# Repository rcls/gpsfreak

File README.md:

GPSfreak — GPS Disciplined Frequency Generator
=================================================

[  ](images/outside-big.jpg)
GPSfreak is a flexible, programmable, high-accuracy, low-jitter, frequency
generator, using GPS as a reference.

There are 5 outputs via SMA connectors, with 4 separately programmable
frequencies derived from 2 PLLs.

The outputs are driven by a Texas Instruments LMK05318b clock generator, and a
U-Blox MAX-10 GPS receiver providing the overall frequency reference.

Power and data are supplied via a USB-C connector (USB FS data rate).  The GPS
unit is available over USB as a CDC ACM serial port.  In addition, there are USB
end-points for device control via the CPU, and Python scripts to drive this.

The hardware is developed using KiCad, and the software using Rust and Python.
There are pdfs of the [schematic](gpsfreak-sch.pdf) and [PCB layout](gpsfreak-pcb.pdf).

License
=======

The hardware designs in this project are all licensed under CERN Open Hardware
Licence, strongly reciprocal, CERN-OHL-S.  (`cern_ohl_s_v2.txt`).

All software in this project is licensed under the GNU GPL v3.  (`COPYING.txt`)

Connectors
==========

[  ](images/inside-big.jpg)

**Outputs 1+** and **1–**
: Complementary high frequency, 3 MHz to 1.6 GHz, 11 dBm nominal output power.
  These can be used together as a differential pair.  AC coupled.

**Output 2**
: High frequency.  3 MHz to 1.6 GHz, 11 dBm nominal output power.  AC coupled.
  There is provision for a balun on the PCB to raise the output power to 14 dBm.

**Output 3**
: Low frequency 3.3 V CMOS.  Sub-1 Hz to 325 MHz.  DC coupled.

**Output 4**
: Mid frequency 3.3 V CMOS.  3 MHz to 325 MHz.  DC coupled.

**GPS Input** for an active L1 and/or L5 GPS antenna.  It provides 3.3 V (or
5 V) antennae power.  The voltage selection is a strap resistor on board.

**USB-C**
: Power (approx 2 W) and data (USB FS).

The high frequency outputs provide complete coverage of 3 MHz to 800 MHz with ≈
pico-Hertz resolution, and then select frequencies to 1.6 GHz.  (There is a
region around 520 MHz where the LMK05318b is operated outside its documented
range, but I have seen no issue with this.)

The outputs are all nominally 50 Ω.  In fact, the LMK05318b appears to have
current-source outputs, so the drive impedance of the high-frequency outputs is
high.  The two CMOS level outputs are each driven by a TLV3601 comparator, from
the datasheet this appears to be a reasonable match for 50 Ω.

There are also pads for 3 internal U.Fl connectors.  One provides an additional
output, one a secondary reference clock input to the LMK05318b, and the last an
output of the GPS timepulse signal.  A possible use is to divert the GPS
timepulse to an external Rubidium clock, and then use that to drive the
secondary reference.

GPS
===

This is a U-Blox MAX-F10S.  (Building the board with other U-Blox MAX or
compatible devices is possible.  The firmware should work with any U-Blox MAX-10
or later device.)

Status LED
==========

There is a status LED next to the USB connector.  This is a three colour RGB
LED.  The LED lights green or red to indicate that the device has PLL lock.
Additionally, the blue component indicates USB activity.

Housing
=======

The board outline is just under 80 mm × 50 mm.  A matching extruded aluminium
housing (80 mm × 50 mm x 20 mm) can be readily obtained from websites such as
AliExpress.

There are small KiCad projects for end-plates (`end-in.kicad_pro` and
`end-out.kicad_pro`), with appropriately sized holes for the connectors and LED.
The screw holes can be counter-sunk with a drill as appropriate.

I recommend checking the board for fit before soldering the components on the
edges (USB and SMA connectors, and the LED).  If necessary, the edges of the
board can be sanded down slightly with sandpaper.

Heat-sinking
------------

The LMK05318b generates a bit of heat, and the board may reach temperatures
30 °C above ambient.  This should not be a problem, but provision is made to
heat-sink the rear of the PCB to the case.

There is an 11 mm × 7 mm exposed copper area backside to the LMK05318b.  Solder
a 2 mm thick copper slug to this, and then cover with a 1.5 mm thick thermal
pad.  The clearance between PCB and housing is 3 mm, so inserting the board into
the housing will apply gentle pressure to the thermal pad.  Chamfer the
appropriate edge of the housing with a file to make inserting the assembly
easier.

(You can find e.g., 2 mm × 10 mm × 100 mm copper bars on AliExpress, from which
an appropriate slug can be cut with a hacksaw.)

Software
========

The device software is a mix of on-board firmware, and Python scripts
(`py/freak.py`) to communicate with the device.  These should work on any OS
that pyusb supports.

The firmware is pretty dumb.  All the frequency planning logic is in the Python
scripts, with the firmware essentially just passing through commands to the GPS
and clock generator.  Frequency plans may be written to flash for autonomous
operation with no USB.

Firmware updates are done via USB DFU.  There is also a Skedd connector breaking
out the CPU SWD with a standard six pin connection.  The CPU boot pin is taken
to a 0.1" header, which can be used to access DFU in case of corrupted firmware.

The Python scripts should work with Python 3.10 or later.

Board Manufacture
=================

The schematic has JLCPCB part numbers for most components.  Components that I've
hand assembled are marked with `exclude from BOM´ and may or may not have the
part number.  Review and change these to suit.

The Makefile should generate Gerber and component files, just run `make`.

The I/O traces (GPS, clock outputs, and USB) are sized for appropriate impedance
on the JLCPCB 4-layer default stack-up (7628).  None of them should be
especially critical, but if you use a different stack-up, then it is worth
double-checking and adjusting them.

Components that I have hand-soldered in preference to using JLCPCB assembly:

* JLCPCB doesn't stock the MAX-F10S.  It is fairly easy to hand-solder.  They do
  stock the cheaper MAX-M10S.
* The USB-C connector, saving a handling fee.
* The SMA connectors.  Position them carefully as they need to align with the
  end-plate holes!  These are edge-launch connectors for a 1.6 mm PCB.  You
  can get these cheaply in bulk from AliExpress.  The ones I used have approx
  12 mm thread length, 18_mm total length including leads.
* The 0402 antennae bias inductor.  The pads are designed for easy hand
  soldering (one is bigger than the other, solder the smaller pad first).
* Likewise, the antennae power PTC fuse and the 74HC1G07 for antennae-short
  detection are hand-soldered, to save assembly costs.  The 74HC1G07 is
  optional.
* The three C0G/NP0 loop-filter caps (C78, C79, C92).
  JLCPCB doesn't have the exact parts.
* The LED.
* The TVS protection diodes I have never populated.  The 0402 pads are designed
  for hand-soldering just like the inductor above.

If you want to keep assembly costs down, then hand soldering many of the ICs is
an option.  This is especially true if you only want one board, as most
manufacturers insist on making multiple!

There is enough space between most of the ICs and surrounding passive components
to get a soldering iron in, but if you are unsure of your soldering equipment
and skills, then review the board layout before committing yourself to that.

Initial Software Install and Configuration
==========================================

This is a rather manual process at the moment.

Firmware build & install
------------------------

For the firmware build, install a recent \`nightly´ rust compiler, along with
cargo, along with the `thumbv8m.main-none-eabihf` target to support the CPU.

Build the firmware with `cargo b`.  This is an alias to build with the correct
compiler options.  The .elf file is left in
`target/thumbv8m.main-none-eabihf/release/freak.elf`.

The initial firmware install can either be done via a SWD dongle (J-Link or
similar) or via DFU USB.  Most SWD programmers support `.elf` files directly.
`dfu-utils` is an unfriendly command line tool, the `dfu.sh` script works for
me.  Note that the shell script assumes you have only one DFU capable device
attached.

The `freak` tool is written in Python.  You need Python 3.10 or later.  The only
additional Python module you need should be `pyusb`, which can be installed
using `pip`.

Initial configuration
---------------------

Run `freak config manufacture`.  This will upload a fairly sane default
configuration for the device, with all outputs at 10 MHz, except for 1 Hz on
output 3.  The DPLL bandwidth is set to 0.3 Hz, which is quite low, and requires
a decent TCXO to achieve lock

If you want to customize the configuration:
 * The uploaded default LMK05318b configuration expects a 8844582 Hz reference
   from the GPS unit.  If you choose something different, be careful about
   near-integer aliasing from the GPS.
 * Loss-of-lock LED indication relies on the GPS turning off that reference
   when GPS signal is lost.  Don't configure the GPS to output the reference
   with no GPS signal (CFG-TP-FREQ_TP1).
 * You can use TICS/Pro to customize the LMK05318b configuration.  Start
   from `py/freak/bw0p3hz_ref8844582.tcs` or another in py/freak/*.tcs.
 * Note that TICS/Pro tends to silently change the lock parameters to values
   that are not good for this hardware.  After running the DPLL script, go to
   the 'Reference Validation' and 'DPLL and BAW flags' tabs, and ensure that
   the Early Window Detector and Lock Thres values are both at least 17 ns.
 * Setting the host-side UART baud rate **must** be done using `freak gps baud`,
   the normal OS serial port baud rate setting is ignored.  I use
   230400 baud; the default 9600 is awfully slow.
 * The initial configuration mentioned above sets `TP-ALIGN_TO_TOW_TP1` to
   False.  This improves short term frequency accuracy, at the expense of a
   small (≈ 3 ppt) long term inaccuracy.

Internal Control Lines
======================

The CPU has various control lines to the GPS and clock chip.  There is UART to
the GPS, and all are on an I2C bus.  In addition, there are connections to:

* EXTINT and RESET lines on GPS.
* PDN, STATUS0, STATUS1 / FDEC and GPIO2 / FINC on the clock chip.  The latter
  two potentially allow some degree of frequency modulation to be achieved e.g.,
  a basic low bit-rate FSK.

Hardware Options
================

The three U.Fl connectors can be soldered.  The GPS timepulse output also
requires soldering a 50 Ω 0603 or similar termination component.

There are pads for a balun on output 2.  If wanted, remove the two 0603
resistors, and solder a 2:1 impedance balun, for a 3 dB increase in output
power.

Before building a device:
 * There are a lot of closely spaced 0402 components on the board.  Unless you
   want the soldering practice, get the majority of the components soldered by
   the board manufacturer.  Most components have JLCPCB part numbers.
 * Review the BOM lists and PCB layout, and check that you are comfortable
   with any components you are going to hand solder.

Component Substitutions
-----------------------

Some notes on possible component substitutions / changes.

**GPS** Any U-Blox MAX-10 is a drop-in replacement.  The software should be
compatible with any U-Blox unit with the newer configuration messages (F9 and
later).  Hardware-wise, any U-Blox 18-pin module should be electrically
compatible.

**LMK05318b** Do not use the non-`b´ LMK05318:
  * With the 3.3 V swing on the reference input, you need to DC couple it, which
    is only supported on the `b´ variant.
  * The software uses the programmable PLL2 denominator.

**C0G/NP0 caps** These are probably overkill for the loop-filter caps.  Feel
free to replace with (smaller and cheaper) X5R / X7R.  In that case I suggest
use parts with a voltage rating of at least 10 V, to minimize the X5R / X7R
voltage dependence.  C78 is only in the schematic because the physically larger
C79 is some distance from the LMK05318b.  If you use smaller components, then
change C78 to 470 nF and remove C79.

If you don't want to hand-solder C78, you could reduce the value to 330 pF
(which JLCPCB has as a basic component).

**Ferrite Beads** I used 100 Ω @ 100 MHz, because JLCPCB had them as basic parts
(no loading fee).  The TI evaluation board has 220 Ω @ 100 MHz.  The choice is
probably not critical, but if you use parts with DC resistance above 0.1 Ω then
double check power consumption and voltage drop on the various voltage rails.

I'm not sure how much difference the ferrite beads make in practice.  If you
remove them entirely, then all the point-of-load 10 µF caps on the power rails
can be replaced by 0.1µF caps.  (Don't change C77, C91 and C93 though.)

**Filter caps** I've used 0402 10 µF caps, where-as the LMK05318b datasheet
suggests 10 µF 0402 plus 0.1 µF 0201.  The main reason is that they are cheaper
with JLCPCB (0201 caps incur loading and assembly fees).

**CPU** Basically any QFN-32 STM32 with USB should be a drop-in replacement
hardware-wise, and require few software modifications—likely only the CPU
initialization and USB clocking will need to change.  Likewise, a CPU in a
different package should require only minor board modifications.

**Voltage regulators** I provisioned 1.8 V as well as 3.3 V in order to reduce
power dissipation.  TI suggests using LDOs to reduce noise.  Having the two
switching regulators before the LDOs reduces power consumption and heating,
without them the LDO would probably overheat.  Beyond that, the power supply
circuitry is fairly arbitrary.

If you switch to a CPU with that supports 1.8 V I/O then you could run the GPS
at 1.8 V also (but in that case, you'll need to supply 3.3 V to the GPS antennae
bias.)

The feedback divider resistors are chosen to avoid JLCPCB loading fees.
Additionally, fine-grained margining of the LDO output voltages can be achieved
by replacing the two 0603 resistors, R56 and R66.

**SMA Connectors** Feel free to replace with through-hole rather than
edge-mount.  In that case, also straighten the board edge, as you no longer need
the cut-outs.  You will need to adjust the position of the mounting-holes in the
end-plates appropriately.

**Programming Header** This can be removed, or swapped for whatever you fancy.
You need to keep one of either the SWD header, or else the boot-pin header, in
order to load firmware.  (Once you have functioning firmware installed, you can
upgrade purely via software command.)

**Temperature Sensor** Populating this is optional.

**LED** This is a common 1206 edge-mount footprint RGB LED.  If you use a
different part, then double or triple check the footprint, and note the odd pad
numbering.

**PTC Fuse** U-Blox example schematics just use a current limiting resistor.
Which would be cheaper. The 74HC1G07 logic gate for antennae short-circuit
sensing is optional.

Hardware Versioning
===================

[TODO - change pin.] CPU pin 13 A7 is reserved for hardware versioning.  The
plan is to use the CPU ADC to read a resistor voltage divider.  To change the
hardware revision, drive with a resistor divider, approx. 10k Thevenin
resistance or less, to N / 25 × VDD, where N is the revision number.  This is
revision 0, so the pin is grounded.

Cost Reduction Opportunities
============================

The MAX-M10S is a cheaper alternative to MAX-F10S, but still performs OK, albeit
with a slightly worse short-term frequency accuracy.

The TCXO can be replaced by a cheaper one.  The phase noise to worry about is
capped above at around 18 kHz by the BAW oscillator, and at low frequencies by
the GPS output.  Using a TCXO rather than an XO is probably not essential, but
does allow us to run the LMK05318b at low bandwidth and smooth out the
once-per-second frequency adjustments from the GPS unit.

The CPU is overkill.  With the current arrangement of dumb firmware & all the
smarts in the Python scripts, a low-end CPU would be just fine.

The temperature sensor is only for development.  Once we know how much heat the
board generates, we can drop it.  Or just use a 1 ¢ thermistor.  There is also
the CPU temperature sensor.

Evaluate whether or not the C0G capacitors on the loop filter are worthwhile.  I
suspect not in realistic conditions.  The 0.47 µF C0G cap could also be replaced
by a through-hole film cap.

The super cap is more or less redundant.  It's only to speed up GPS start-up
after a short power outage, but we are likely to be always on anyway.

The output balun on output 2 is not worth the cost.  I've marked it as DNP
in the schematic.

The `freak` tool
================

The `freak` tool can perform various operations as well as setting the output
frequencies.  Everything has a `--help` option which is hopefully helpful.

`freak freq` with no arguments displays the current output frequencies.  Give it
arguments to set the output frequencies.  The units default to MHz, but an
explicit unit of Hz, kHz or GHz may be given.  Rational numbers (e.g., 100/3)
are accepted, and avoid rounding errors inherent with decimals (33.333333).

`freak plan` can carry out the frequency planning computations without writing
them to the device.  This is useful to explore what is possible.

`freak drive` can display and set the various output drive strengths.

`freak clock get/set` and get and set individual clock generator registers.  The
TI documentation lists most but not all of these.  The file
`py/freak/lmk05318b.list` has a few additions that I've gleaned from other
sources.

`freak gps get/set` likewise get and set GPS config registers.

For more advanced programming of the LMK05318b, your best option is to generate
a `.tcs` file with the TI TICS/Pro tool, and write to the device with `freak
clock upload`.

`freak info`, `freak clock status`, `freak gps info` and `freak gps status` all
output various bits of hardware information and status, in varying degrees of
understandability.

`freak gps changes` shows the difference between the current GPS configuration
and the factory defaults.

`freak clock dump` or `freak gps dump` print the entire clock generator or GPS
configuration, respectively.

Known Issues
============

If frequency planning fails, then `freak` tends to die with an unfriendly
assertion failure rather than a useful error message.  Ditto various other error
conditions.  Problems with the communication to the GPS unit likely result in
hangs.

Change Log
==========

Current
-------

Enlarge the exposed pad backside to the clock chip to be 11 mm × 7 mm instead of
7 mm square.

Don't have the LED overhanging the board edge.  Change all the LED resistors to
0603 for easier swapping.  Plate the panel cut-out opening for the LED.

Remove the unnecessary strap resistor on the GPS timepulse U.Fl connector.

Hardware version 1.0
--------------------

Two built.  Major revision from prototype.  git rev 496bb8c98727dc07.

Prototype
---------

Hardware was git rev 24c0655742e6f093.  Only one built.

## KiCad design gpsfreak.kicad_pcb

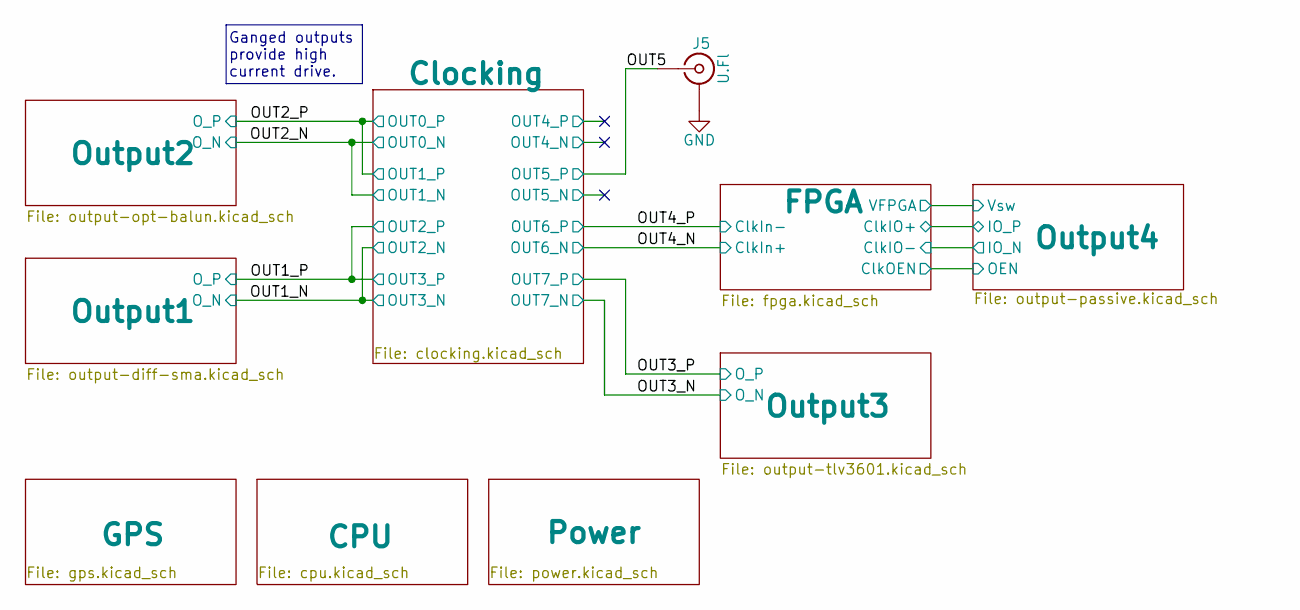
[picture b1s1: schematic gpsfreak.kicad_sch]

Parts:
J5: U.Fl; U.FL_Hirose_U.FL-R-SMT-1_Vertical

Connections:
/OUT5: J5.1 (In); also elsewhere on the board
GND: J5.2 (Ext); also elsewhere on the board

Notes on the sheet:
Ganged outputs provide high current drive.

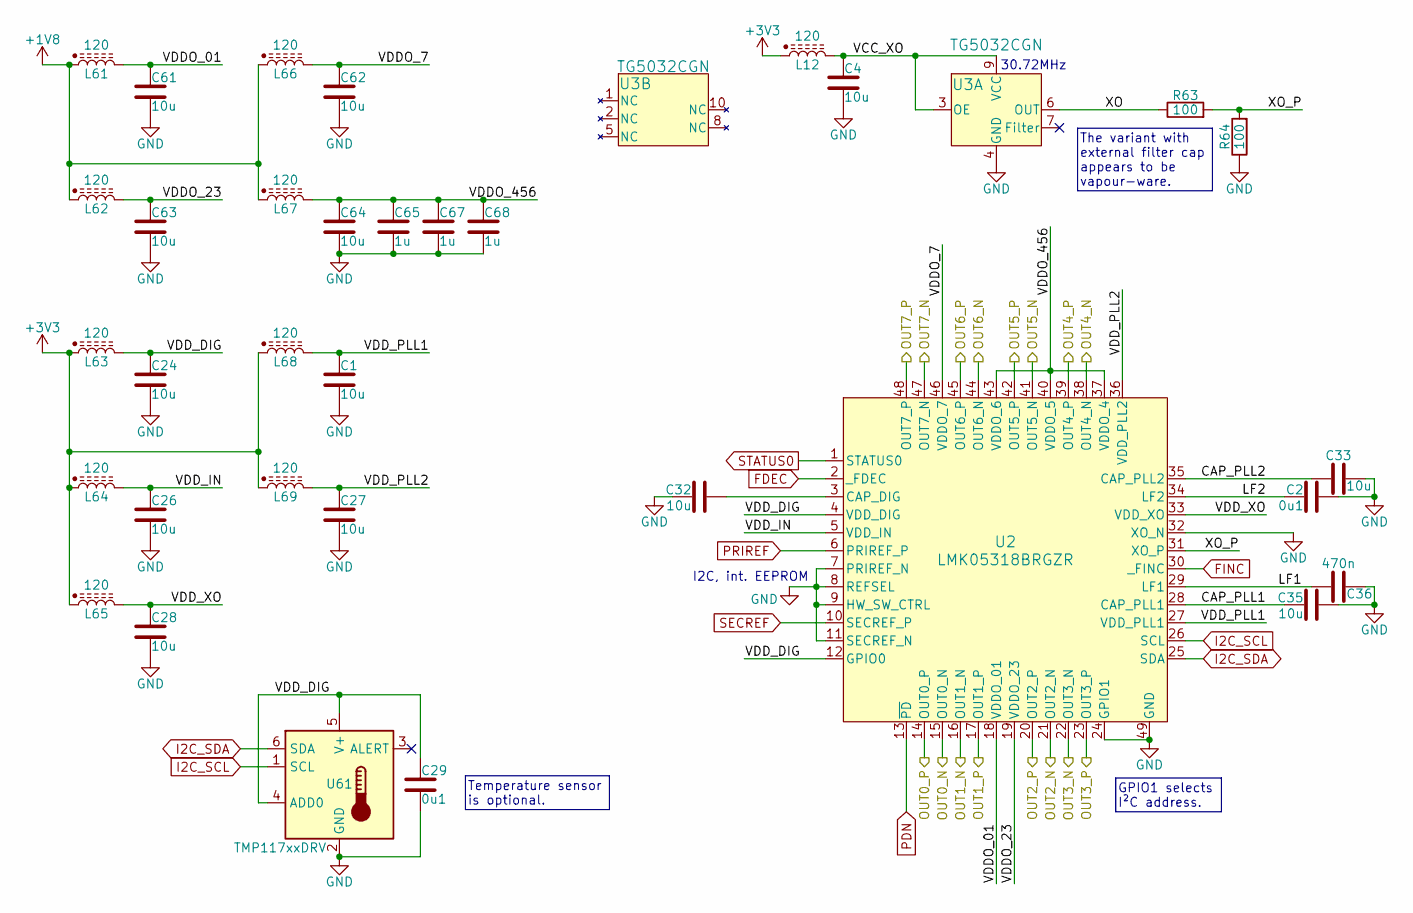
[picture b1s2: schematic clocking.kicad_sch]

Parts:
C1, C4, C24, C26, C27, C28, C32, C33, C35, C61, C62, C63, C64: 10u; C_0402_1005Metric; LCSC C315248
C2: 0u1; C0704; LCSC C20044553
C29: 0u1; C_0402_1005Metric; LCSC C307331
C36: 470n; C_1206_3216Metric; LCSC C21082486
C65, C67, C68: 1u; C_0402_1005Metric; LCSC C52923
L12, L61, L62, L63, L64, L65, L66, L67, L68, L69: 120; L_0603_1608Metric; LCSC C14709
R63, R64: 100; R_0402_1005Metric; LCSC C25076
U2: LMK05318BRGZR; QFN-48-1EP_7x7mm_P0.5mm_EP5.1x5.1mm; LCSC C3611586
U3: TG5032CGN; QFN10_TG5032CGN 40.0000M-CAGHNA0_EPS; LCSC C2891970
U61: TMP117xxDRV; WSON-6-1EP_2x2mm_P0.65mm_EP1x1.6mm

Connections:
+1V8: L61.1, L62.1, L66.1, L67.1; also elsewhere on the board
+3V3: L12.1, L63.1, L64.1, L65.1, L68.1, L69.1; also elsewhere on the board
/Clocking/CAP_PLL1: C35.2, U2.28 (CAP_PLL1)
/Clocking/CAP_PLL2: C33.2, U2.35 (CAP_PLL2)
/Clocking/LF1: C36.1, U2.29 (LF1)
/Clocking/LF2: C2.1, U2.34 (LF2)
/Clocking/OUT4_N: U2.38 (OUT4_N)
/Clocking/OUT4_P: U2.39 (OUT4_P)
/Clocking/OUT5_N: U2.41 (OUT5_N)
/Clocking/VCC_XO: C4.1, L12.2, U3.3 (OE), U3.9 (VCC)
/Clocking/VDDO_01: C61.1, L61.2, U2.18 (VDDO_01)
/Clocking/VDDO_7: C62.1, L66.2, U2.46 (VDDO_7)
/Clocking/VDDO_23: C63.1, L62.2, U2.19 (VDDO_23)
/Clocking/VDDO_456: C64.1, C65.1, C67.1, C68.1, L67.2, U2.37 (VDDO_4), U2.40 (VDDO_5), U2.43 (VDDO_6)
/Clocking/VDD_DIG: C24.1, C29.1, L63.2, U2.4 (VDD_DIG), U2.12 (GPIO0), U61.4 (ADD0), U61.5 (V+)
/Clocking/VDD_IN: C26.1, L64.2, U2.5 (VDD_IN)
/Clocking/VDD_PLL1: C1.1, L68.2, U2.27 (VDD_PLL1)
/Clocking/VDD_PLL2: C27.1, L69.2, U2.36 (VDD_PLL2)
/Clocking/VDD_XO: C28.1, L65.2, U2.33 (VDD_XO)
/Clocking/XO: R63.1, U3.6 (OUT)
/Clocking/XO_P: R63.2, R64.2, U2.31 (XO_P)
/OUT1_N: U2.21 (OUT2_N), U2.22 (OUT3_N); also elsewhere on the board
/OUT1_P: U2.20 (OUT2_P), U2.23 (OUT3_P); also elsewhere on the board
/OUT2_N: U2.15 (OUT0_N), U2.16 (OUT1_N); also elsewhere on the board
/OUT2_P: U2.14 (OUT0_P), U2.17 (OUT1_P); also elsewhere on the board
/OUT3_N: U2.47 (OUT7_N); also elsewhere on the board
/OUT3_P: U2.48 (OUT7_P); also elsewhere on the board
/OUT4_N: U2.44 (OUT6_N); also elsewhere on the board
/OUT4_P: U2.45 (OUT6_P); also elsewhere on the board
/OUT5: U2.42 (OUT5_P); also elsewhere on the board
FDEC: U2.2 (_FDEC); also elsewhere on the board
FINC: U2.30 (_FINC); also elsewhere on the board
GND: C1.2, C2.2, C4.2, C24.2, C26.2, C27.2, C28.2, C29.2, C32.1, C33.1, C35.1, C36.2, C61.2, C62.2, C63.2, C64.2, C65.2, C67.2, C68.2, R64.1, U2.7 (PRIREF_N), U2.8 (REFSEL), U2.9 (HW_SW_CTRL), U2.11 (SECREF_N), U2.24 (GPIO1), U2.32 (XO_N), U2.49 (GND), U3.4 (GND), U61.2 (GND), U61.7 (GND); also elsewhere on the board
I2C_SCL: U2.26 (SCL), U61.1 (SCL); also elsewhere on the board
I2C_SDA: U2.25 (SDA), U61.6 (SDA); also elsewhere on the board
unnamed: C32.2, U2.3 (CAP_DIG)
PDN: U2.13 (~PD); also elsewhere on the board
PRIREF: U2.6 (PRIREF_P); also elsewhere on the board
SECREF: U2.10 (SECREF_P); also elsewhere on the board
STATUS0: U2.1 (STATUS0); also elsewhere on the board

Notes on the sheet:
I2C, int. EEPROM
30.72MHz
Temperature sensor is optional.
GPIO1 selects I²C address.
The variant with external filter cap appears to be vapour-ware.

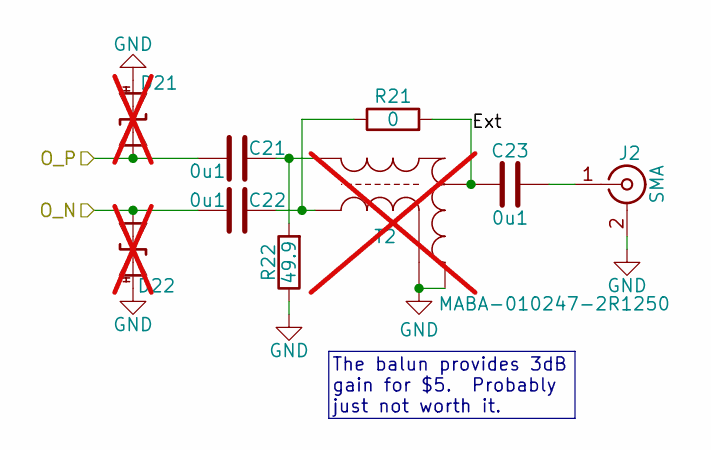
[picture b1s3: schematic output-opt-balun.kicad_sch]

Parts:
C21, C22, C23: 0u1; C_0402_1005Metric; LCSC C307331
D21, D22: D_TVS; HHS_0402; not fitted
J2: SMA; SMA_EdgeMount
R21: 0; R_0603_1608Metric; LCSC C21189
R22: 49.9; R_0603_1608Metric; LCSC C23185
T2: MABA-010247-2R1250; XFMR_MABA-007159-000000; LCSC C3305191; not fitted

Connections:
/OUT2_N: C22.1, D22.1 (A1); also elsewhere on the board
/OUT2_P: C21.1, D21.1 (A1); also elsewhere on the board
/Output2/Ext: C23.1, R21.2, T2.4
GND: D21.2 (A2), D22.2 (A2), J2.2 (Ext), R22.1, T2.2, T2.5; also elsewhere on the board
unnamed: C21.2, R22.2, T2.1
unnamed: C22.2, R21.1, T2.3
unnamed: C23.2, J2.1 (In)

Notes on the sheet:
The balun provides 3dB gain for $5. Probably just not worth it.

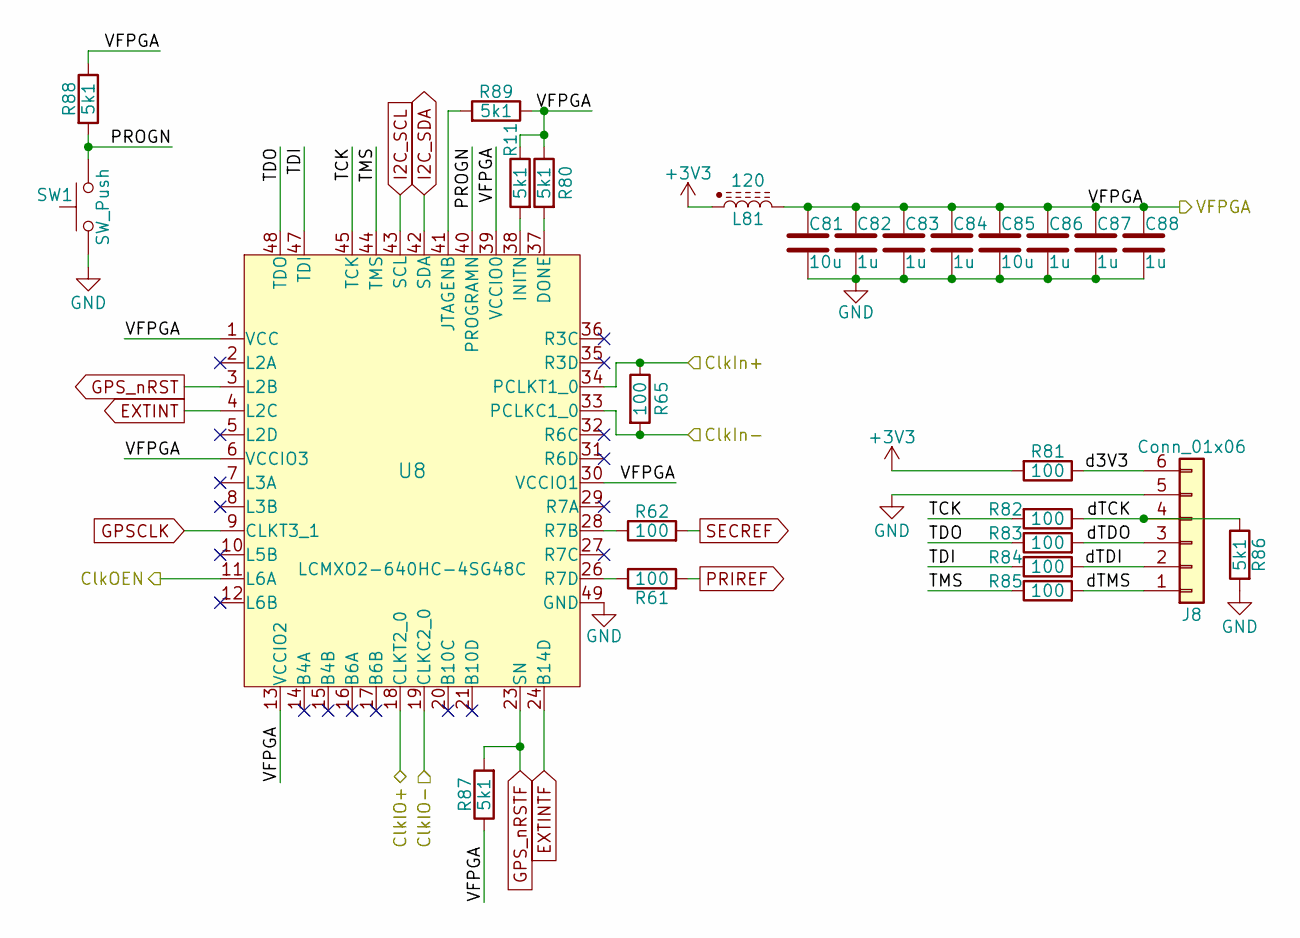
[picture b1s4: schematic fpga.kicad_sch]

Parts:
C81, C85: 10u; C_0402_1005Metric; LCSC C315248
C82, C83, C84, C86, C87, C88: 1u; C_0402_1005Metric; LCSC C52923
J8: Conn_01x06; PinHeader_1x06_P2.54mm_Vertical
L81: 120; L_0603_1608Metric; LCSC C14709
R11, R80, R86, R87, R88, R89: 5k1; R_0402_1005Metric; LCSC C25905
R61, R62, R65, R81, R82, R83, R84, R85: 100; R_0402_1005Metric; LCSC C25076
SW1: SW_Push; SW_SPST_TS-1088-xR020; LCSC C720477
U8: LCMXO2-640HC-4SG48C; QFN-48-1EP_7x7mm_P0.5mm_EP5.45x5.45mm; LCSC C1521838

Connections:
+3V3: L81.1, R81.2; also elsewhere on the board
/FPGA/ClkIO+: U8.18 (CLKT2_0); also elsewhere on the board
/FPGA/ClkIO-: U8.19 (CLKC2_0); also elsewhere on the board
/FPGA/ClkOEN: U8.11 (L6A); also elsewhere on the board
/FPGA/PROGN: R88.2, SW1.2, U8.40 (PROGRAMN)
/FPGA/TCK: R82.2, U8.45 (TCK)
/FPGA/TDI: R84.1, U8.47 (TDI)
/FPGA/TDO: R83.1, U8.48 (TDO)
/FPGA/TMS: R85.1, U8.44 (TMS)
/FPGA/VFPGA: C81.1, C82.1, C83.1, C84.1, C85.1, C86.1, C87.1, C88.1, L81.2, R11.1, R80.1, R87.1, R88.1, R89.1, U8.1 (VCC), U8.6 (VCCIO3), U8.13 (VCCIO2), U8.22 (VCCIO2), U8.25 (VCC), U8.30 (VCCIO1), U8.39 (VCCIO0), U8.46 (VCCIO0); also elsewhere on the board
/FPGA/d3V3: J8.6, R81.1
/FPGA/dTCK: J8.4, R82.1, R86.1
/FPGA/dTDI: J8.2, R84.2
/FPGA/dTDO: J8.3, R83.2
/FPGA/dTMS: J8.1, R85.2
/OUT4_N: R65.1, U8.34 (PCLKT1_0); also elsewhere on the board
/OUT4_P: R65.2, U8.33 (PCLKC1_0); also elsewhere on the board
EXTINT: U8.4 (L2C); also elsewhere on the board
EXTINTF: U8.24 (B14D); also elsewhere on the board
GND: C81.2, C82.2, C83.2, C84.2, C85.2, C86.2, C87.2, C88.2, J8.5, R86.2, SW1.1, U8.49 (GND); also elsewhere on the board
GPSCLK: U8.9 (CLKT3_1); also elsewhere on the board
GPS_nRST: U8.3 (L2B); also elsewhere on the board
GPS_nRSTF: R87.2, U8.23 (SN); also elsewhere on the board
I2C_SCL: U8.43 (SCL); also elsewhere on the board
I2C_SDA: U8.42 (SDA); also elsewhere on the board
unnamed: R62.1, U8.28 (R7B)
unnamed: R61.1, U8.26 (R7D)
unnamed: R89.2, U8.41 (JTAGENB)
unnamed: R11.2, U8.38 (INITN)
unnamed: R80.2, U8.37 (DONE)
PRIREF: R61.2; also elsewhere on the board
SECREF: R62.2; also elsewhere on the board

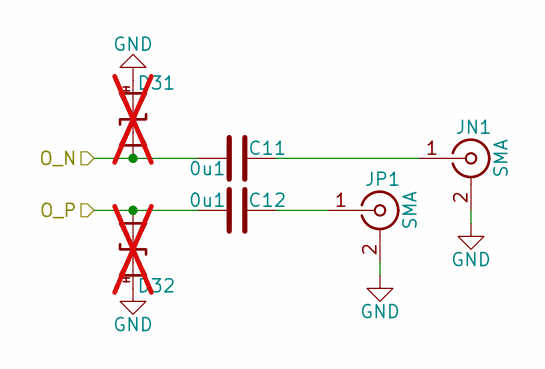
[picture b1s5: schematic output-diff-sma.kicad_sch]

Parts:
C11, C12: 0u1; C_0402_1005Metric; LCSC C307331
D31, D32: D_TVS; HHS_0402; not fitted
JN1: SMA; SMA_EdgeMount
JP1: SMA; SMA_EdgeMount

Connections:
/OUT1_N: C11.1, D31.1 (A1); also elsewhere on the board
/OUT1_P: C12.1, D32.1 (A1); also elsewhere on the board
GND: D31.2 (A2), D32.2 (A2), JN1.2 (Ext), JP1.2 (Ext); also elsewhere on the board
unnamed: C11.2, JN1.1 (In)
unnamed: C12.2, JP1.1 (In)

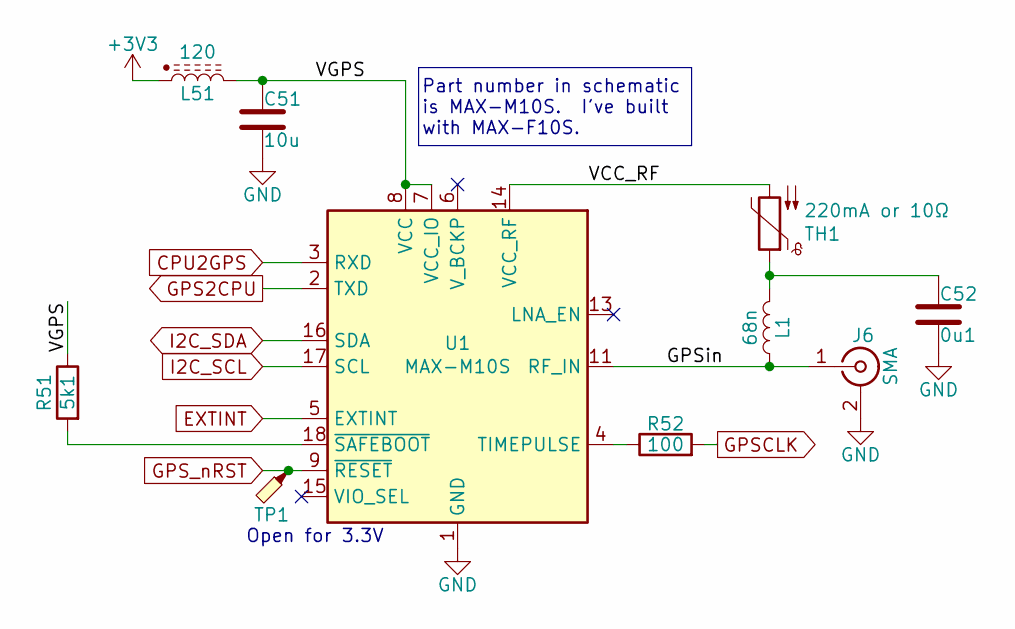
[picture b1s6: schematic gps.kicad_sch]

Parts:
C51: 10u; C_0402_1005Metric; LCSC C315248
C52: 0u1; C_0402_1005Metric; LCSC C307331
J6: SMA; SMA_EdgeMount
L1: 68n; HHS_0402; LCSC C3224079
L51: 120; L_0603_1608Metric; LCSC C14709
R51: 5k1; R_0402_1005Metric; LCSC C25905
R52: 100; R_0402_1005Metric; LCSC C25076
TH1: 220mA or 10Ω; R_0603_1608Metric; LCSC C22859
TP1: TestPoint_Probe; TestPoint
U1: MAX-M10S; ublox_MAX; LCSC C4153167

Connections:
+3V3: L51.1; also elsewhere on the board
/GPS/GPSin: J6.1 (In), L1.1, U1.11 (RF_IN)
/GPS/VCC_RF: TH1.2, U1.14 (VCC_RF)
/GPS/VGPS: C51.1, L51.2, R51.1, U1.7 (VCC_IO), U1.8 (VCC)
CPU2GPS: U1.3 (RXD); also elsewhere on the board
EXTINT: U1.5 (EXTINT); also elsewhere on the board
GND: C51.2, C52.2, J6.2 (Ext), U1.1 (GND), U1.10 (GND), U1.12 (GND); also elsewhere on the board
GPS2CPU: U1.2 (TXD); also elsewhere on the board
GPSCLK: R52.2; also elsewhere on the board
GPS_nRST: TP1.1 (1_1), U1.9 (~RESET); also elsewhere on the board
I2C_SCL: U1.17 (SCL); also elsewhere on the board
I2C_SDA: U1.16 (SDA); also elsewhere on the board
unnamed: C52.1, L1.2, TH1.1
unnamed: R52.1, U1.4 (TIMEPULSE)
unnamed: R51.2, U1.18 (~SAFEBOOT)

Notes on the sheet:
Open for 3.3V
Part number in schematic is MAX-M10S. I've built with MAX-F10S.

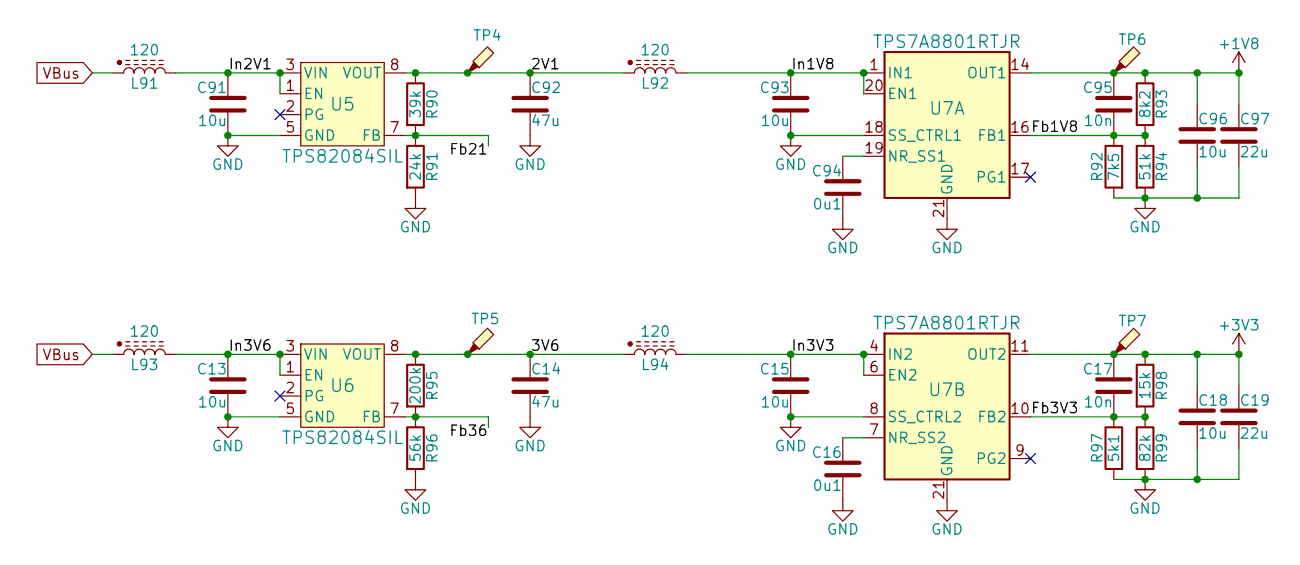
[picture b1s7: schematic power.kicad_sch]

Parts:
C13, C15, C91, C93: 10u; C_0603_1608Metric; LCSC C96446
C14, C92: 47u; C_0805_2012Metric; LCSC C16780
C16, C94: 0u1; C_0402_1005Metric; LCSC C307331
C17, C95: 10n; C_0402_1005Metric; LCSC C15195
C18, C96: 10u; C_0402_1005Metric; LCSC C315248
C19, C97: 22u; C_0603_1608Metric; LCSC C59461
L91, L92, L93, L94: 120; L_0603_1608Metric; LCSC C14709
R90: 39k; R_0402_1005Metric; LCSC C25783
R91: 24k; R_0402_1005Metric; LCSC C25769
R92: 7k5; R_0402_1005Metric; LCSC C25918
R93: 8k2; R_0402_1005Metric; LCSC C25924
R94: 51k; R_0402_1005Metric; LCSC C25794
R95: 200k; R_0402_1005Metric; LCSC C25764
R96: 56k; R_0402_1005Metric; LCSC C25796
R97: 5k1; R_0402_1005Metric; LCSC C25905
R98: 15k; R_0402_1005Metric; LCSC C25756
R99: 82k; R_0603_1608Metric; LCSC C23254
TP4: 2V2; TestPoint
TP5, TP6, TP7: TestPoint_Probe; TestPoint
U5, U6: TPS82084SIL; SIL0008C_SMD_NV; LCSC C468248
U7: TPS7A8801RTJR; QFN-20-1EP_4x4mm_P0.5mm_EP2.7x2.7mm; LCSC C485919

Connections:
+1V8: C95.1, C96.1, C97.1, R93.1, TP6.1 (1_1), U7.14 (OUT1), U7.15 (OUT1); also elsewhere on the board
+3V3: C17.1, C18.1, C19.1, R98.1, TP7.1 (1_1), U7.11 (OUT2), U7.12 (OUT2); also elsewhere on the board
/Power/2V1: C92.1, L92.1, R90.1, TP4.1 (1_1), U5.8 (VOUT)
/Power/3V6: C14.1, L94.1, R95.1, TP5.1 (1_1), U6.8 (VOUT)
/Power/Fb1V8: C95.2, R92.1, R93.2, R94.1, U7.16 (FB1)
/Power/Fb3V3: C17.2, R97.1, R98.2, R99.1, U7.10 (FB2)
/Power/Fb21: R90.2, R91.1, U5.7 (FB)
/Power/Fb36: R95.2, R96.1, U6.7 (FB)
/Power/In1V8: C93.1, L92.2, U7.1 (IN1), U7.2 (IN1), U7.20 (EN1)
/Power/In2V1: C91.1, L91.2, U5.1 (EN), U5.3 (VIN), U5.4 (VIN)
/Power/In3V3: C15.1, L94.2, U7.4 (IN2), U7.5 (IN2), U7.6 (EN2)
/Power/In3V6: C13.1, L93.2, U6.1 (EN), U6.3 (VIN), U6.4 (VIN)
GND: C13.2, C14.2, C15.2, C16.2, C18.2, C19.2, C91.2, C92.2, C93.2, C94.2, C96.2, C97.2, R91.2, R92.2, R94.2, R96.2, R97.2, R99.2, U5.5 (GND), U5.6 (GND), U5.9 (PAD), U6.5 (GND), U6.6 (GND), U6.9 (PAD), U7.3 (GND), U7.8 (SS_CTRL2), U7.13 (GND), U7.18 (SS_CTRL1), U7.21 (GND); also elsewhere on the board
unnamed: C94.1, U7.19 (NR_SS1)
unnamed: C16.1, U7.7 (NR_SS2)
VBus: L91.1, L93.1; also elsewhere on the board

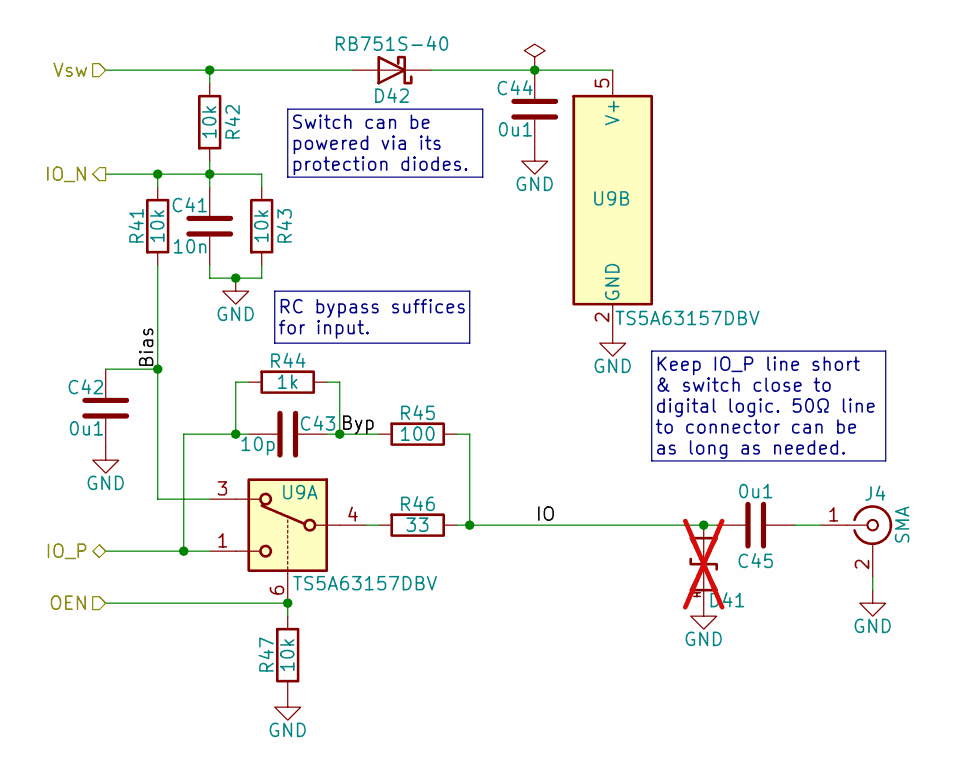
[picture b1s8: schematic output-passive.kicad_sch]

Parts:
C41: 10n; C_0402_1005Metric; LCSC C15195
C42, C44, C45: 0u1; C_0402_1005Metric; LCSC C307331
C43: 10p; C_0402_1005Metric; LCSC C32949
D41: D_TVS; HHS_0402; not fitted
D42: RB751S-40; D_SOD-523; LCSC C7502700
J4: SMA; SMA_EdgeMount
R41, R42, R43, R47: 10k; R_0402_1005Metric; LCSC C25744
R44: 1k; R_0402_1005Metric; LCSC C11702
R45: 100; R_0402_1005Metric; LCSC C25076
R46: 33; R_0402_1005Metric; LCSC C25105
U9: TS5A63157DBV; SOT-363_SC-70-6; LCSC C133575

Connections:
/FPGA/ClkIO+: C43.1, R44.2, U9.1; also elsewhere on the board
/FPGA/ClkIO-: C41.1, R41.1, R42.2, R43.1; also elsewhere on the board
/FPGA/ClkOEN: R47.2, U9.6; also elsewhere on the board
/FPGA/VFPGA: D42.2 (A), R42.1; also elsewhere on the board
/Output4/Bias: C42.1, R41.2, U9.3
/Output4/Byp: C43.2, R44.1, R45.2
/Output4/IO: C45.1, D41.1 (A1), R45.1, R46.1
GND: C41.2, C42.2, C44.2, D41.2 (A2), J4.2 (Ext), R43.2, R47.1, U9.2 (GND); also elsewhere on the board
unnamed: C44.1, D42.1 (K), U9.5 (V+)
unnamed: C45.2, J4.1 (In)
unnamed: R46.2, U9.4

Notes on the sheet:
Switch can be powered via its protection diodes.
RC bypass suffices for input.
Keep IO_P line short & switch close to digital logic. 50Ω line to connector can be as long as needed.

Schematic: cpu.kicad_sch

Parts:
C71, C72, C73, C75, C76: 1u; C_0402_1005Metric; LCSC C52923
C74: 10u; C_0402_1005Metric; LCSC C315248
C77: 4u7; C_0402_1005Metric; LCSC C23733
C78: 10n; C_0402_1005Metric; LCSC C15195
D1: 5V6; D_SOD-323; LCSC C19077435
D2: LED_GBAR; LED_RGB_SIDE; LCSC C389528
J7: USB_C_Receptacle_16P; USB_C_Receptacle_GCT_USB4105-xx-A_16P_TopMnt_Horizontal; LCSC C2765186
J9: Skedd; Skedd6
J13: Boot; PinHeader_1x02_P2.54mm_Vertical
L71: 120; L_0603_1608Metric; LCSC C14709
R1, R2, R3, R4, R5, R6: 100; R_0402_1005Metric; LCSC C25076
R7: 100k; R_0402_1005Metric; LCSC C25741
R71, R72: 5k1; R_0402_1005Metric; LCSC C25905
R73: 330; R_0603_1608Metric; LCSC C23138
R74: 2k7; R_0603_1608Metric; LCSC C13167
R75: 1k; R_0603_1608Metric; LCSC C21190
R76, R77, R78, R79: 10k; R_0402_1005Metric; LCSC C25744
TP3: TestPoint_Probe; TestPoint
U4: STM32H503KBUx; QFN-32-1EP_5x5mm_P0.5mm_EP3.45x3.45mm; LCSC C22385521
U71: USBLC6-2SC6; SOT-666-6; LCSC C15999

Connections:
+3V3: D2.1 (C), J13.1, L71.1, R1.2; also elsewhere on the board
/CPU/BOOT0: R6.2, R7.1, U4.31 (BOOT0)
/CPU/Blue: R73.2, U4.25 (PA15(JTDI))
/CPU/CC1: J7.A5 (CC1), R71.2
/CPU/CC2: J7.B5 (CC2), R72.2
/CPU/CPU_nRST: C78.1, R3.2, U4.4 (NRST)
/CPU/DBG_TX: R5.2, U4.26 (USART3_TX)
/CPU/Green: R74.2, U4.27 (PB4(NJTRST))
/CPU/HWID: R78.1, R79.2, U4.9 (PA3)
/CPU/Red: R75.2, U4.28 (PB5)
/CPU/SWCLK: R4.2, U4.24 (DEBUG_JTCK-SWCLK)
/CPU/SWDIO: R2.2, U4.23 (DEBUG_JTMS-SWDIO)
/CPU/USB_D+: J7.A6 (D+), J7.B6 (D+), U4.22 (USB_DP), U71.3 (I/O2), U71.4 (I/O2)
/CPU/USB_D-: J7.A7 (D-), J7.B7 (D-), U4.21 (USB_DM), U71.1 (I/O1), U71.6 (I/O1)
/CPU/VCPU: C74.1, C75.1, C76.1, L71.2, R76.2, R77.2, R78.2, U4.1 (VDD), U4.5 (VDDA), U4.17 (VDD), U4.20 (PA9)
/CPU/d3V3: J9.1, R1.1
/CPU/dBOOT: J13.2, R6.1
/CPU/dRST: J9.3, R3.1
/CPU/dSWC: J9.4, R4.1
/CPU/dSWD: J9.2, R2.1
/CPU/dTX: J9.6, R5.1
CPU2GPS: U4.19 (USART2_TX); also elsewhere on the board
EXTINTF: U4.12 (PA6); also elsewhere on the board
FDEC: U4.13 (TIM2_CH3); also elsewhere on the board
FINC: U4.11 (TIM2_CH1); also elsewhere on the board
GND: C71.1, C72.1, C73.1, C74.2, C75.2, C76.2, C77.2, C78.2, D1.2 (A), J7.A1 (GND), J7.A12 (GND), J7.B1 (GND), J7.B12 (GND), J7.SH (SHIELD), J9.5, R7.2, R71.1, R72.1, R79.1, TP3.1 (1_1), U4.2 (PC14), U4.3 (PC15), U4.6 (PA0), U4.7 (PA1), U4.8 (PA2), U4.33 (VSS), U71.2 (GND); also elsewhere on the board
GPS2CPU: U4.18 (USART2_RX); also elsewhere on the board
GPS_nRSTF: U4.15 (PB1); also elsewhere on the board
I2C_SCL: R76.1, U4.29 (I2C1_SCL); also elsewhere on the board
I2C_SDA: R77.1, U4.30 (I2C1_SDA); also elsewhere on the board
unnamed: D2.2 (B), R73.1
unnamed: D2.3 (G), R74.1
unnamed: D2.4 (R), R75.1
unnamed: C77.1, U4.16 (VCAP)
PDN: U4.10 (PA4); also elsewhere on the board
STATUS0: U4.14 (PB0); also elsewhere on the board
VBus: C71.2, C72.2, C73.2, D1.1 (K), J7.A4 (VBUS), J7.A9 (VBUS), J7.B4 (VBUS), J7.B9 (VBUS), U71.5 (VBUS); also elsewhere on the board

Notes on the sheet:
EN_REF2
EN_OUT3
USB_VBUS
EN_OUT4
PA3 is used as a board revision identifier.
FIXME - can we stick at 0V? Default FPGA load will be backwards compatible.

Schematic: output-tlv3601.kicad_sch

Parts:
C3: 10u; C_0402_1005Metric; LCSC C315248
D35: D_TVS; HHS_0402; not fitted
J3: SMA; SMA_EdgeMount
L31: 120; L_0603_1608Metric; LCSC C14709
R31, R32: 100k; R_0402_1005Metric; LCSC C25741
R33: 100; R_0402_1005Metric; LCSC C25076
U31: TLV3601DCKR; SOT-353_SC-70-5; LCSC C2974371

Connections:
+3V3: L31.1, R32.2; also elsewhere on the board
/OUT3_N: R32.1, R33.2, U31.4 (-); also elsewhere on the board
/OUT3_P: R31.2, R33.1, U31.3 (+); also elsewhere on the board
/Output3/Ext: D35.1 (A1), J3.1 (In), U31.1
GND: C3.2, D35.2 (A2), J3.2 (Ext), R31.1, U31.2 (V-); also elsewhere on the board
unnamed: C3.1, L31.2, U31.5 (V+)

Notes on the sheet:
The TLV3601 output resistance appears to be around 80Ω, compared with the target 50Ω.

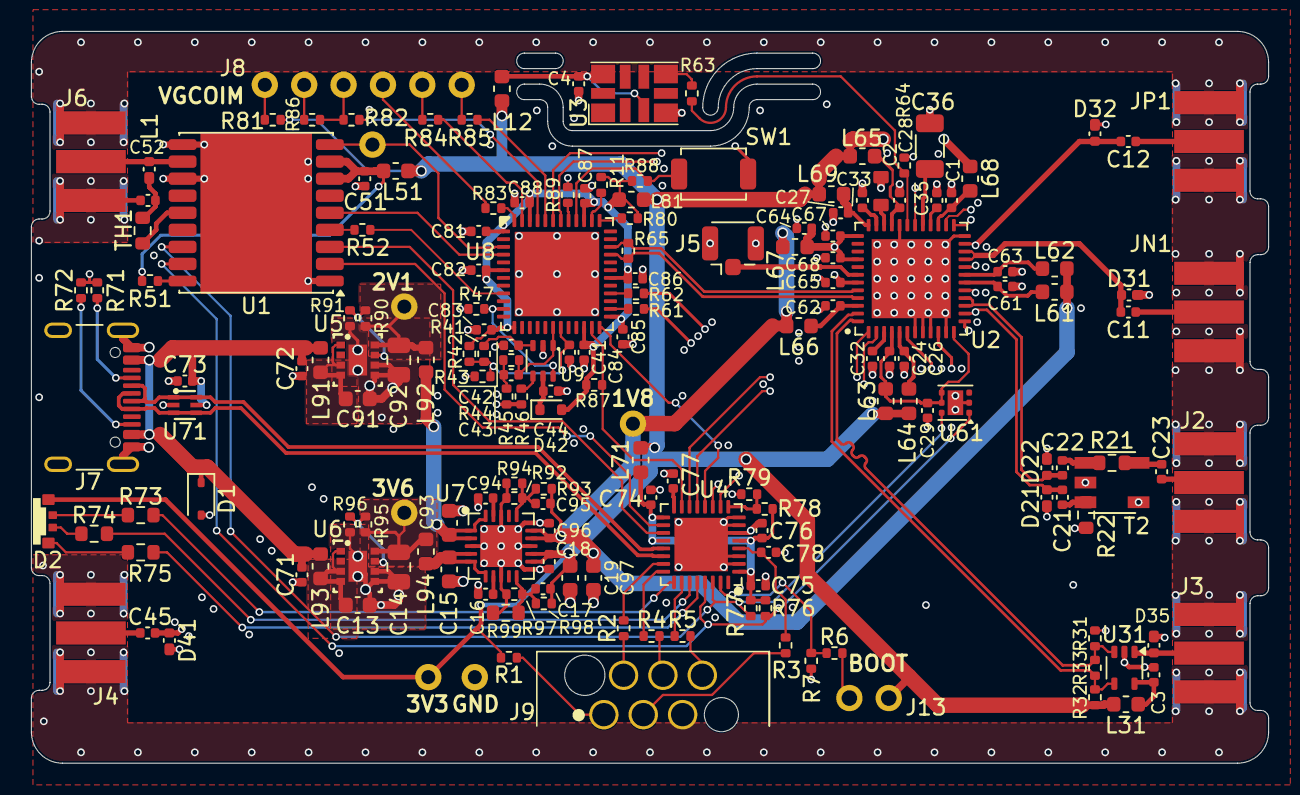
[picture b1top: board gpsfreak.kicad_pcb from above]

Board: 4 copper layers, 79.8 x 47.2 mm, 178 parts (0 on the bottom side), 120 nets.
